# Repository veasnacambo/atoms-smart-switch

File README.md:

# Atoms Smart Switch

Smart switch retrofit module based on ESP-IDF.

## Version 1 goal
- 1 or 2 channel first
- relay output
- manual switch input
- local wireless control
- offline operation
- safe PCB architecture
- low cost

## Repository structure
- firmware/  -> ESP-IDF firmware
- hardware/  -> schematic, PCB, hardware notes
- docs/      -> architecture, API, test plan

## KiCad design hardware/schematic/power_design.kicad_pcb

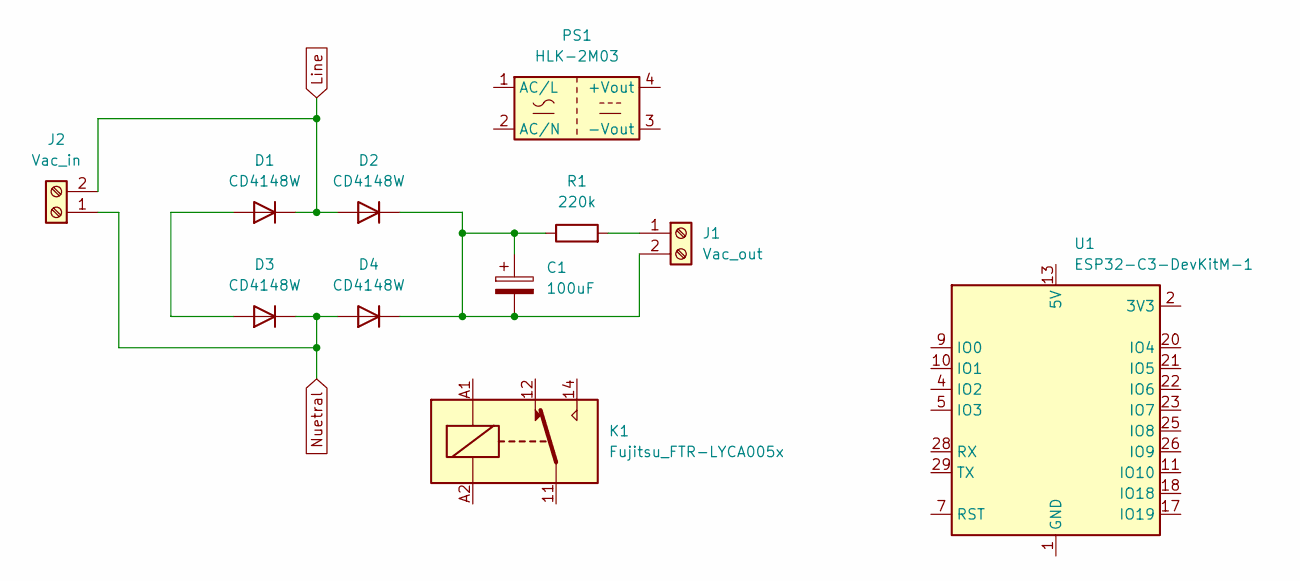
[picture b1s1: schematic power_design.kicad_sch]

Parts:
C1: 100uF; CP_Elec_6.3x3
D1, D2, D3, D4: CD4148W; D_0805_2012Metric
J1: Vac_out; TerminalBlock_MaiXu_MX126-5.0-02P_1x02_P5.00mm
J2: Vac_in; TerminalBlock_MaiXu_MX126-5.0-02P_1x02_P5.00mm
K1: Fujitsu_FTR-LYCA005x; Relay_SPDT_Fujitsu_FTR-LYCA005x_FormC_Vertical
PS1: HLK-2M03; Converter_ACDC_Hi-Link_HLK-2Mxx
R1: 220k; R_0201_0603Metric
U1: ESP32-C3-DevKitM-1

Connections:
Line: D1.1 (K), D2.2 (A), J2.2
unnamed: D1.2 (A), D3.2 (A)
unnamed: C1.1, C1.2, D2.1 (K), D4.1 (K), J1.2, R1.1
unnamed: J1.1, R1.2
unnamed: U1.2 (3V3), U1.3 (3V3)
unnamed: U1.13 (5V), U1.14 (5V)
unnamed: U1.1 (GND), U1.6 (GND), U1.8 (GND), U1.12 (GND), U1.15 (GND), U1.16 (GND), U1.19 (GND), U1.24 (GND), U1.27 (GND), U1.30 (GND)
Nuetral: D3.1 (K), D4.2 (A), J2.1

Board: 2 copper layers, 11 parts (0 on the bottom side), 8 nets, no tracks yet.

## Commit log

2026-03-26 Initial project structure: smart switch V1 (ESP-IDF)
2026-03-26 Initial workspace setup for smart switch V1 demo
2026-03-26 Clean firmware project structure
2026-03-26 Add relay and switch input bring-up for demo
2026-03-29 software update
